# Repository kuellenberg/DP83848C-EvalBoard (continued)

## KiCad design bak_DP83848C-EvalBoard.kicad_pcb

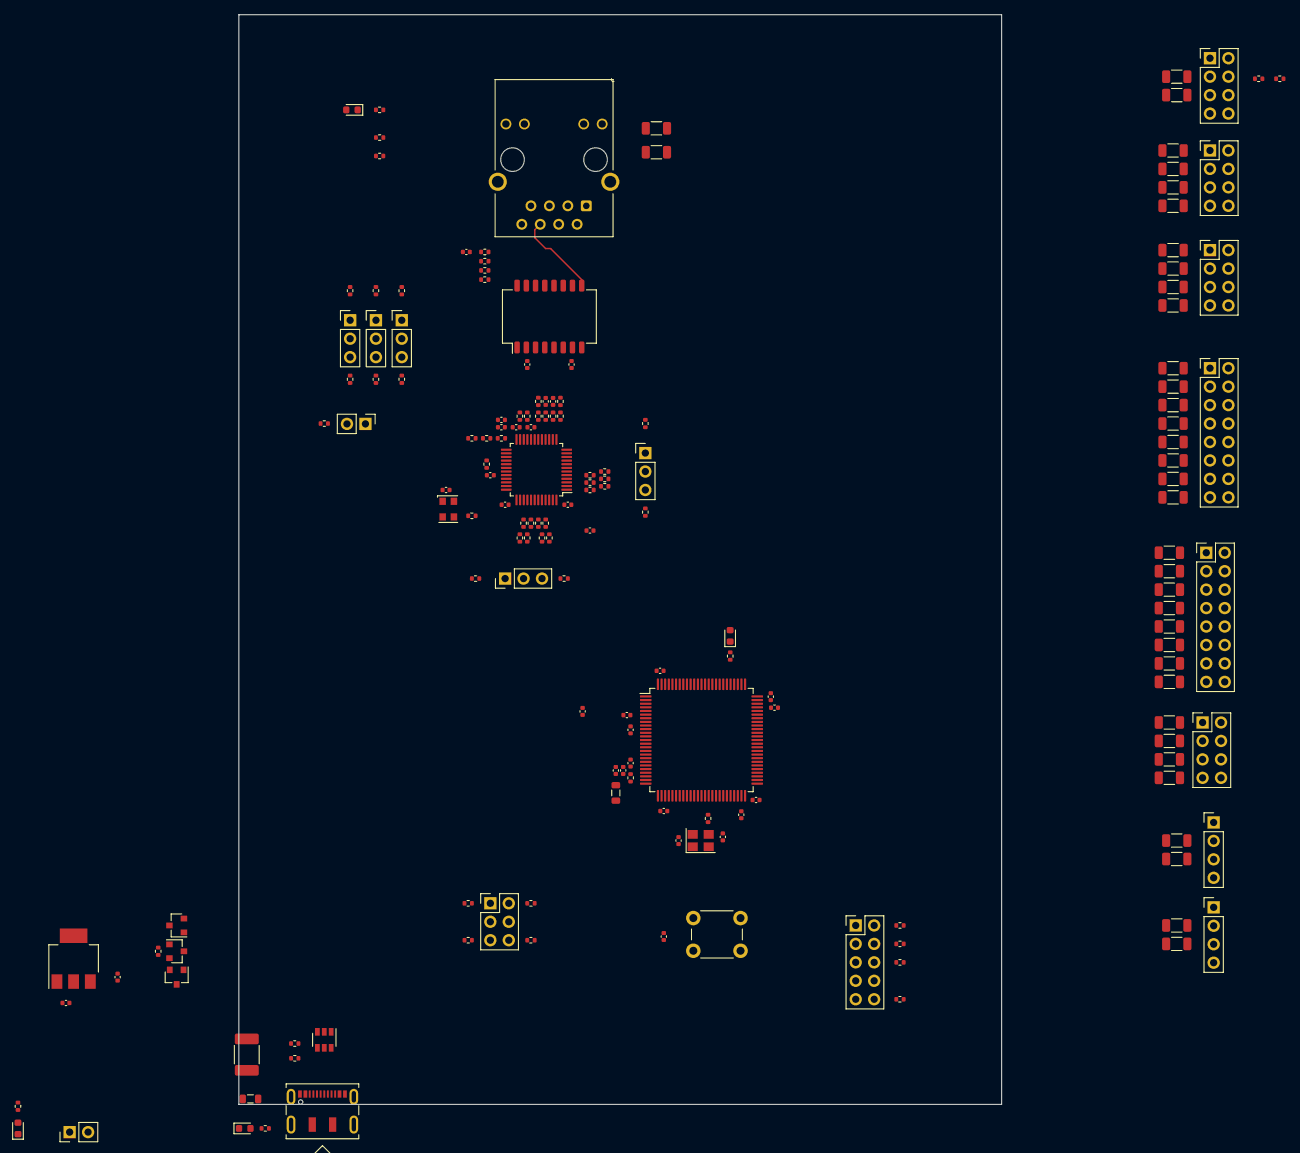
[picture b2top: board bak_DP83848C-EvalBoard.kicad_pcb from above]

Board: 4 copper layers, 105.0 x 150.0 mm, 167 parts (0 on the bottom side), 175 nets.

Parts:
C1: 47uF; C_0402_1005Metric
C2: 22uF; C_0402_1005Metric
C3, C5, C6, C7, C8, C9, C11, C12, C13, C14, C15, C19, C20, C22, C23, C24, C25, C26, C27, C29: 100nF; C_0402_1005Metric
C4, C10: 10uF; C_0402_1005Metric
C16: 1500pF; C_0402_1005Metric
C17: 4.7uF; C_0402_1005Metric
C18, C21: 2.2uF; C_0402_1005Metric
C28: 1uF; C_0402_1005Metric
C30, C31: TBD; C_0402_1005Metric
D1: GR; LED_0603_1608Metric
D2: YE; LED_0603_1608Metric
D3: YL; LED_0603_1608Metric
D4: BL; LED_0603_1608Metric
F1: 200mA; Fuse_1812_4532Metric_Castellated
J1, J2: Conn_02x08_Odd_Even; PinHeader_2x08_P2.54mm_Vertical
J3, J6, J7, J8: Conn_02x04_Odd_Even; PinHeader_2x04_P2.54mm_Vertical
J4, J5: Conn_01x04; PinHeader_1x04_P2.54mm_Vertical
J9: Conn_01x02; PinHeader_1x02_P2.54mm_Vertical
J10: RJ45_LED_Shielded; RJ45_Hanrun_HR911105A
J11: USB_C_Receptacle_USB2.0; DX07S016JA3R1500
J12: Conn_02x05_Odd_Even; PinHeader_2x05_P2.54mm_Vertical
JP1: Conn_01x02; PinHeader_1x02_P2.54mm_Vertical
JP2, JP3, JP4, JP5, JP6: Conn_01x03; PinHeader_1x03_P2.54mm_Vertical
JP7: Conn_02x03_Odd_Even; PinHeader_2x03_P2.54mm_Vertical
L1: 600R@100MHz; L_0805_2012Metric
L2: 100@100MHz; L_0805_2012Metric
Q1, Q3: AO3401A; SOT-23
Q2: AO3400A; SOT-23
R1, R2: 4k7; R_0402_1005Metric
R3, R5, R44, R47, R48: 220; R_0402_1005Metric
R4: 47k; R_0402_1005Metric
R6, R23, R24, R34, R35, R36, R37, R42, R43, R45, R46, R49, R50: 2.2k; R_0402_1005Metric
R7, R8, R9, R10, R11, R12, R13, R14, R15, R16, R17, R18, R19, R20, R60, R61, R62, R63: 33; R_0402_1005Metric
R21: 1.5k; R_0402_1005Metric
R22, R30, R31: 0; R_0402_1005Metric
R25, R26, R27, R28: 49.9; R_0402_1005Metric
R29: 4.7k; R_0402_1005Metric
R32: 150; R_0402_1005Metric
R33: 22; R_0402_1005Metric
R38, R39, R40, R41: 75; R_0402_1005Metric
R51: 0R; R_0402_1005Metric
R52: 100; R_0402_1005Metric
R53, R54, R55, R56: 10k; R_0402_1005Metric
R57, R58: 5.1k; R_0402_1005Metric
R59: 1M; R_0402_1005Metric
R64, R65, R66, R67, R68, R69, R70, R71, R72, R73, R74, R75, R76, R77, R78, R79, R80, R81, R82, R83, R84, R85, R86, R87, R88, R89, R90, R91, R92, R93, R94, R95, R96, R97: 33; R_1206_3216Metric
R98, R99: 0; R_1206_3216Metric
SW1: SW_Push; SW_PUSH_6mm
T1: H1102NL; Transformer_Pulse_H1100NL
U1: AMS1117-3.3; SOT-223-3_TabPin2
U2: DP83848C; LQFP-48_7x7mm_P0.5mm
U3: STM32F407VGTx; LQFP-100_14x14mm_P0.5mm
U4: USBLC6-2SC6; SOT-23-6
X1: 50MHz; Oscillator_SMD_EuroQuartz_XO32-4Pin_3.2x2.5mm
Y1: 25MHz; Crystal_SMD_3225-4Pin_3.2x2.5mm

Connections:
+3V3: C2.1, C3.1, C4.1, C5.1, C6.1, C7.1, C14.1, C15.1, C17.1, C20.1, C22.1, C23.1, C24.1, C25.1, C26.1, C27.1, D3.2, D4.2, J3.2, J3.4, J4.1, J5.1, J6.2, J6.4, J7.2, J7.4, J8.1, J8.2, J8.8, J10.10, J10.12, J12.1, L1.1, R21.2, R23.1, R24.1, R30.1, R31.1, R34.1, R36.1, R42.1, R45.1, R49.1, R53.1, R55.2, T1.2, T1.7, U1.2, U2.22, U2.32, U2.48, U3.6, U3.11, U3.19, U3.28, U3.50, U3.75, U3.100, X1.1, X1.4
+5V: C1.1, Q1.2, Q3.2, R4.1, U1.3
/ADC0: R72.1, U3.23
/ADC1: R73.1, U3.26
/ADC2: R74.1, U3.31
/ADC3: R75.1, U3.35
/ADC4: R76.1, U3.36
/ADC5: R77.1, U3.15
/ADC6: R78.1, U3.17
/ADC7: R79.1, U3.18
/ETH_CRS_DV: R20.2, U3.32
/ETH_MDC: U2.31, U3.16
/ETH_MDIO: R21.1, U2.30, U3.25
/ETH_RXD0: R13.2, U3.33
/ETH_RXD1: R14.2, U3.34
/ETH_TX_D0: R7.2, U3.51
/ETH_TX_D1: R8.2, U3.52
/ETH_TX_EN: R12.2, U3.48
/GPIO0: R64.1, U3.97
/GPIO1: R65.1, U3.98
/GPIO2: R66.1, U3.1
/GPIO3: R67.1, U3.2
/GPIO4: R68.1, U3.3
/GPIO5: R69.1, U3.4
/GPIO6: R70.1, U3.5
/GPIO7: R71.1, U3.38
/MCU/BOOT0: JP7.3, U3.94
/MCU/BOOT1: JP7.4, U3.37
/MCU/I2C1_SCL: R97.2, U3.92
/MCU/I2C1_SDA: R96.2, U3.93
/MCU/NRST: C19.1, R63.1, SW1.1, U3.14
/MCU/OSC_IN: C30.2, U3.12, Y1.1
/MCU/OSC_OUT: R59.2, U3.13
/MCU/SPI1_MISO: R88.2, U3.90
/MCU/SPI1_MOSI: R89.2, U3.91
/MCU/SPI1_NSS: R91.2, U3.29
/MCU/SPI1_SCK: R90.2, U3.30
/MCU/SPI2_MISO: R92.2, U3.53
/MCU/SPI2_MOSI: R93.2, U3.54
/MCU/SPI2_NSS: R95.2, U3.96
/MCU/SPI2_SCK: R94.2, U3.47
/MCU/STATUS_LED: R52.2, U3.81
/MCU/SWCLK: R61.1, U3.76
/MCU/SWDIO: R60.1, U3.72
/MCU/SWO: R62.1, U3.89
/MCU/USB_CONN_D+: J11.A6, J11.B6, U4.6
/MCU/USB_CONN_D-: J11.A7, J11.B7, U4.4
/MCU/USB_FS_D+: U3.71, U4.1
/MCU/USB_FS_D-: U3.70, U4.3
/MCU/VCAP_1: C18.1, U3.49
/MCU/VCAP_2: C21.1, U3.73
/PHY/AN0: JP4.2, R44.1, U2.28
/PHY/AN1: JP5.2, R48.2, U2.27
/PHY/AN_EN: JP6.2, R47.2, U2.26
/PHY/MII_MODE: JP2.2, R19.2
/PHY/PFB: C8.1, C9.1, C10.1, C13.1, U2.18, U2.23, U2.37
/PHY/RD+: R27.1, T1.6, U2.14
/PHY/RD-: R28.2, T1.8, U2.13
/PHY/RX+: J10.3, T1.11
/PHY/RX-: J10.6, T1.9
/PHY/RXC: R38.1, T1.10
/PHY/SNI_MODE: JP3.2, R10.2
/PHY/TD+: R25.1, T1.1, U2.17
/PHY/TD-: R26.2, T1.3, U2.16
/PHY/TX+: J10.1, T1.16
/PHY/TX-: J10.2, T1.14
/PHY/TXC: R39.1, T1.15
/PHY/~RESET: JP1.1, U2.29
/PSU/VEXT: J9.1, Q1.3, Q2.1, Q3.1, R3.1
/TMR1: R80.1, U3.40
/TMR2: R81.1, U3.42
/TMR3: R82.1, U3.44
/TMR4: R83.1, U3.45
/USART1_RX: R84.1, U3.69
/USART1_TX: R85.1, U3.68
/USART2_RX: R86.1, U3.87
/USART2_TX: R87.1, U3.86
GND: C1.2, C2.2, C3.2, C4.2, C5.2, C6.2, C7.2, C8.2, C9.2, C10.2, C11.2, C12.2, C13.2, C14.2, C15.2, C17.2, C18.2, C19.2, C20.2, C21.2, C22.2, C23.2, C24.2, C25.2, C26.2, C27.2, C28.2, C29.2, C30.1, C31.2, D1.1, D2.1, J1.2, J1.4, J1.6, J1.8, J1.10, J1.12, J1.14, J1.16, J2.2, J2.4, J2.6, J2.8, J2.10, J2.12, J2.14, J2.16, J3.6, J3.8, J4.4, J5.4, J6.6, J6.8, J7.6, J7.8, J8.7, J9.2, J11.A1, J11.A12, J12.3, J12.5, J12.9, Q2.2, R6.1, R33.1, R35.1, R37.1, R43.1, R46.1, R50.1, R54.1, R56.2, R57.1, R58.1, R98.1, R99.1, SW1.2, U1.1, U2.15, U2.19, U2.35, U2.36, U2.47, U3.10, U3.20, U3.27, U3.74, U3.99, U4.2, X1.2, Y1.2, Y1.4
GNDPWR: C16.2, J10.SH, R98.2, R99.2
unnamed: C11.1, R25.2, R26.1, R30.2
unnamed: C12.1, R27.2, R28.1, R31.2
unnamed: C16.1, R38.2, R39.2, R40.2, R41.2
unnamed: C31.1, R59.1, Y1.3
unnamed: D1.2, R3.2
unnamed: D2.2, R5.2
unnamed: D3.1, R48.1
unnamed: D4.1, R52.1
unnamed: F1.2, L2.2
unnamed: J1.1, R64.2
unnamed: J1.3, R65.2
unnamed: J1.5, R66.2
unnamed: J1.7, R67.2
unnamed: J1.9, R68.2
unnamed: J1.11, R69.2
unnamed: J1.13, R70.2
unnamed: J1.15, R71.2
unnamed: J2.1, R72.2
unnamed: J2.3, R73.2
unnamed: J2.5, R74.2
unnamed: J2.7, R75.2
unnamed: J2.9, R76.2
unnamed: J2.11, R77.2
unnamed: J2.13, R78.2
unnamed: J2.15, R79.2
unnamed: J3.1, R80.2
unnamed: J3.3, R81.2
unnamed: J3.5, R82.2
unnamed: J3.7, R83.2
unnamed: J4.2, R84.2
unnamed: J4.3, R85.2
unnamed: J5.2, R86.2
unnamed: J5.3, R87.2
unnamed: J6.1, R88.1
unnamed: J6.3, R89.1
unnamed: J6.5, R90.1
unnamed: J6.7, R91.1
unnamed: J7.1, R92.1
unnamed: J7.3, R93.1
unnamed: J7.5, R94.1
unnamed: J7.7, R95.1
unnamed: J8.3, R2.2, R96.1
unnamed: J8.4, R2.1
unnamed: J8.5, R1.2, R97.1
unnamed: J8.6, R1.1
unnamed: J10.4, J10.5, R40.1
unnamed: J10.7, J10.8, R41.1
unnamed: J10.9, R44.2
unnamed: J10.11, R47.1
unnamed: J11.A4, J11.A9, L2.1, U4.5
unnamed: J11.A5, R57.2
unnamed: J11.B5, R58.2
unnamed: J12.2, R60.2
unnamed: J12.4, R61.2
unnamed: J12.6, R62.2
unnamed: J12.10, R63.2
unnamed: JP1.2, R6.2
unnamed: JP2.1, R34.2
unnamed: JP2.3, R35.2
unnamed: JP3.1, R36.2
unnamed: JP3.3, R37.2
unnamed: JP4.1, R42.2
unnamed: JP4.3, R43.2
unnamed: JP5.1, R45.2
unnamed: JP5.3, R46.2
unnamed: JP6.1, R49.2
unnamed: JP6.3, R50.2
unnamed: JP7.1, R53.2
unnamed: JP7.2, R55.1
unnamed: JP7.5, R54.2
unnamed: JP7.6, R56.1
unnamed: Q1.1, Q2.3, R4.2
unnamed: R7.1, U2.3
unnamed: R8.1, U2.4
unnamed: R9.1, U2.5
unnamed: R10.1, U2.6
unnamed: R11.1, U2.1
unnamed: R12.1, U2.2
unnamed: R13.1, U2.43
unnamed: R14.1, U2.44
unnamed: R15.1, U2.45
unnamed: R16.1, U2.46
unnamed: R17.1, U2.38
unnamed: R18.1, U2.41
unnamed: R19.1, U2.39
unnamed: R20.1, U2.40
unnamed: R22.1, U2.34
unnamed: R22.2, X1.3
unnamed: R23.2, U2.20
unnamed: R24.2, U2.21
unnamed: R29.1, R32.2
unnamed: R29.2, U2.24
unnamed: R32.1, R33.2
unnamed: R51.1, U3.21
VDDA: C28.1, C29.1, L1.2, R51.2, U3.22
VUSB: F1.1, Q3.3, R5.1

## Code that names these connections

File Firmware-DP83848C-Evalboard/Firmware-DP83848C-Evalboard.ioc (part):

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PH0-OSC_IN.Signal=RCC_OSC_IN
PA7.Mode=RMII
Mcu.UserName=STM32F407VGTx
PC4.Signal=ETH_RXD0
PD0.GPIO_Label=LED
PA11.Mode=Device_Only
PC5.Mode=RMII
PB11.Signal=ETH_TX_EN
PB13.Signal=ETH_TXD1
RCC.SYSCLKSource=RCC_SYSCLKSOURCE_PLLCLK
PA13.Signal=SYS_JTMS-SWDIO
PA12.Signal=USB_OTG_FS_DP
PB11.Mode=RMII
PD0.Signal=GPIO_Output
PA1.Signal=ETH_REF_CLK
PH0-OSC_IN.Mode=HSE-External-Oscillator
RCC.HSE_VALUE=25000000
board=custom
PA1.Mode=RMII
PA14.Mode=Serial_Wire
PH1-OSC_OUT.Signal=RCC_OSC_OUT
PA13.Mode=Serial_Wire
Mcu.Name=STM32F407V(E-G)Tx
PA2.Signal=ETH_MDIO
PH1-OSC_OUT.Mode=HSE-External-Oscillator
RCC.SYSCLKFreq_VALUE=120000000
Mcu.Package=LQFP100
PB12.Mode=RMII
PA12.Mode=Device_Only
PA11.Signal=USB_OTG_FS_DM
PA14.Signal=SYS_JTCK-SWCLK
PD0.GPIOParameters=GPIO_Label
PA2.Mode=RMII
PC5.Signal=ETH_RXD1
PB13.Mode=RMII
PC1.Signal=ETH_MDC
PB12.Signal=ETH_TXD0
PC4.Mode=RMII
PC1.Mode=RMII
PA7.Signal=ETH_CRS_DV

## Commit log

2020-12-18 Work in progress
2020-12-19 Component placement
2020-12-20 Test...
2020-12-20 Placement
2020-12-21 Routing
2020-12-22 Layout
2020-12-24 Added ESD protection
2021-01-06 DRC and minor changes
2021-01-06 Text
2021-01-07 Revert "Text"
    This reverts commit 08ad5a624c52bb92dd714530982a715c3c379f2a.
2021-01-07 Minor changes
2021-02-22 Minor changes and production files
2021-03-13 Firmware
